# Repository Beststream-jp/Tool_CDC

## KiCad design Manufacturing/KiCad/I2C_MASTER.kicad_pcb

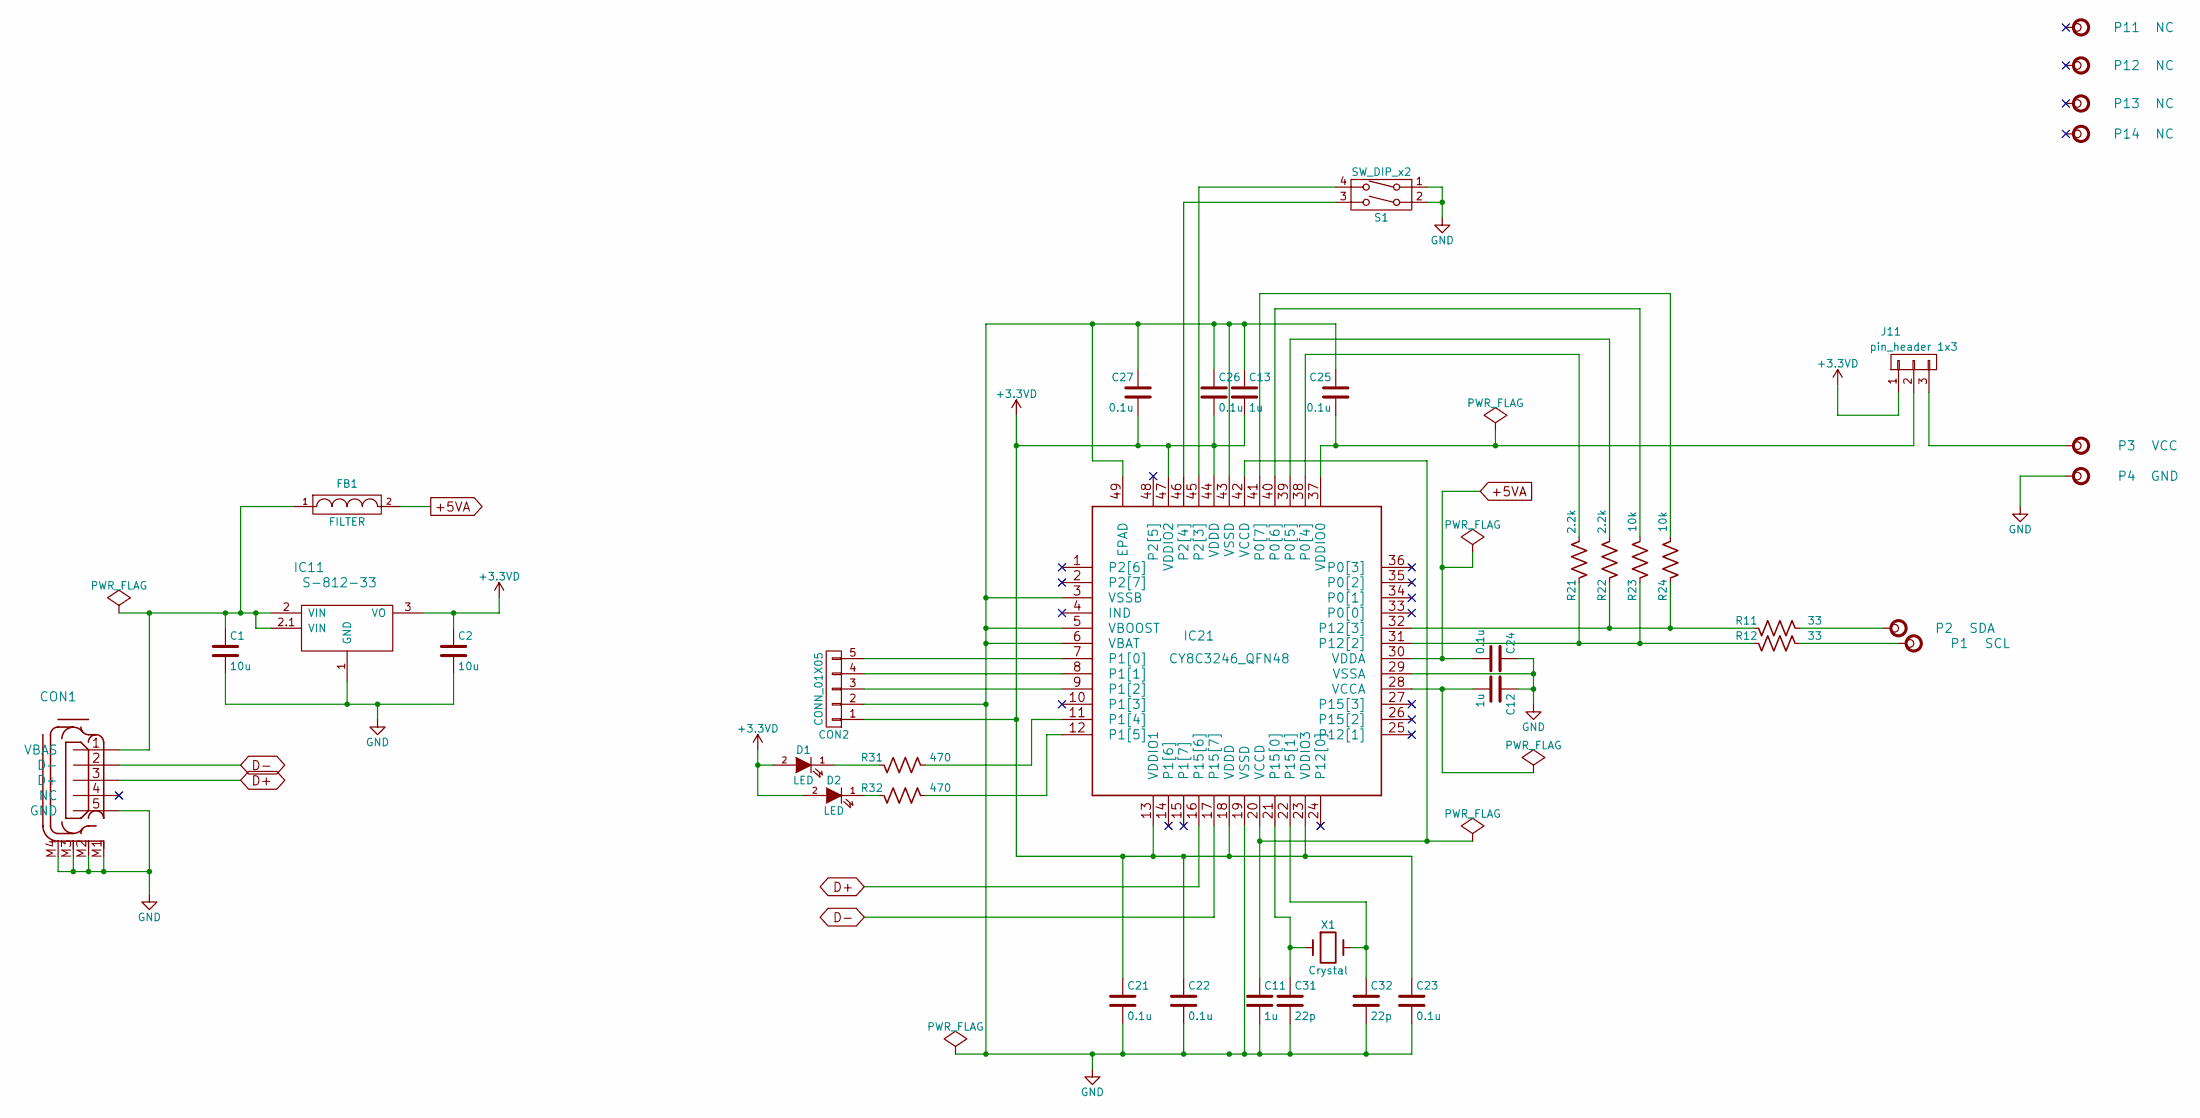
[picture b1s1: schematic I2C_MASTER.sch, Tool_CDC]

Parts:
C1, C2: 10u; C_0805
C11, C12, C13: 1u; C_0603
C21, C22, C23, C24, C25, C26, C27: 0.1u; C_0603
C31, C32: 22p; C_0603
CON1: MINI-USB-SCHIELD-32005-301_32005-301; 32005-301
CON2: CONN_01X05; JST_PH_B5B-PH-K_05x2.00mm_Straight
D1, D2: LED; LED-3MM
FB1: FILTER; C_0603_HandSoldering
IC11: S-812-33; SOT89-3_Housing
IC21: CY8C3246_QFN48; QFN-48-1EP_7x7mm_Pitch0.5mm
J11: pin_header 1x3; 22-23-2031
P1: SCL; SolderWirePad_single_0-8mmDrill
P2: SDA; SolderWirePad_single_0-8mmDrill
P3: VCC; SolderWirePad_single_0-8mmDrill
P4: GND; SolderWirePad_single_0-8mmDrill
P11, P12, P13, P14: NC; MountingHole_3.2mm_M3
R11, R12: 33; R_0603
R21, R22: 2.2k; R_0603
R23, R24: 10k; R_0603
R31, R32: 470; R_0603
S1: SW_DIP_x2; EDG-02
X1: Crystal; HC-49V

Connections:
+3V3: C2.1, C13.2, C21.1, C22.1, C23.1, C26.2, C27.2, CON2.1, D1.2 (A), D2.2 (A), IC11.3 (VO), IC21.13 (VDDIO1), IC21.18 (VDDD), IC21.23 (VDDIO3), IC21.44 (VDDD), IC21.47 (VDDIO2), J11.1
+5VA: C24.2, FB1.2, IC21.30 (VDDA)
D+: CON1.3 (D+), IC21.16 (P15[6])
D-: CON1.2 (D-), IC21.17 (P15[7])
GND: C1.2, C2.2, C11.2, C12.1, C13.1, C21.2, C22.2, C23.2, C24.1, C25.1, C26.1, C27.1, C31.2, C32.2, CON1.5 (GND), CON1.M1 (S1), CON1.M2 (S2), CON1.M3 (S3), CON1.M4 (S4), CON2.2, IC11.1 (GND), IC21.3 (VSSB), IC21.5 (VBOOST), IC21.6 (VBAT), IC21.19 (VSSD), IC21.29 (VSSA), IC21.43 (VSSD), IC21.49 (EPAD), P4.1, S1.1, S1.2
unnamed: C1.1, CON1.1 (VBAS), FB1.1, IC11.2 (VIN), IC11.2.1 (VIN)
unnamed: C11.1, IC21.20 (VCCD), IC21.42 (VCCD)
unnamed: C12.2, IC21.28 (VCCA)
unnamed: C25.2, IC21.37 (VDDIO0), J11.2
unnamed: C31.1, IC21.21 (P15[0]), X1.1
unnamed: C32.1, IC21.22 (P15[1]), X1.2
unnamed: CON2.3, IC21.9 (P1[2])
unnamed: CON2.4, IC21.8 (P1[1])
unnamed: CON2.5, IC21.7 (P1[0])
unnamed: D1.1 (K), R31.2
unnamed: D2.1 (K), R32.2
unnamed: IC21.11 (P1[4]), R31.1
unnamed: IC21.12 (P1[5]), R32.1
unnamed: IC21.31 (P12[2]), R12.2, R21.2, R23.2
unnamed: IC21.32 (P12[3]), R11.2, R22.2, R24.2
unnamed: IC21.38 (P0[4]), R21.1
unnamed: IC21.39 (P0[5]), R22.1
unnamed: IC21.40 (P0[6]), R23.1
unnamed: IC21.41 (P0[7]), R24.1
unnamed: IC21.45 (P2[3]), S1.4
unnamed: IC21.46 (P2[4]), S1.3
unnamed: J11.3, P3.1
unnamed: P1.1, R12.1
unnamed: P2.1, R11.1

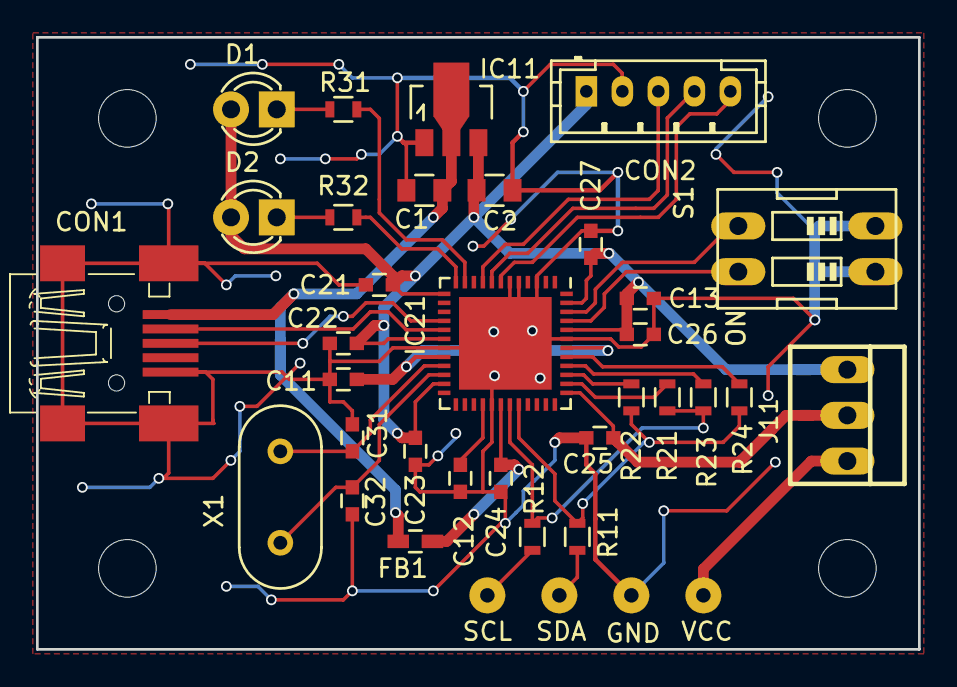
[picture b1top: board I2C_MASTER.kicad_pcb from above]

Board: 2 copper layers, 49.0 x 34.0 mm, 40 parts (0 on the bottom side), 29 nets.

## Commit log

2016-10-13 files added initial commit
2016-10-22 Software added
2016-10-25 report file added.
2016-10-25 cad files added.
2016-10-25 gerber folder
2016-10-25 gerber files added.
